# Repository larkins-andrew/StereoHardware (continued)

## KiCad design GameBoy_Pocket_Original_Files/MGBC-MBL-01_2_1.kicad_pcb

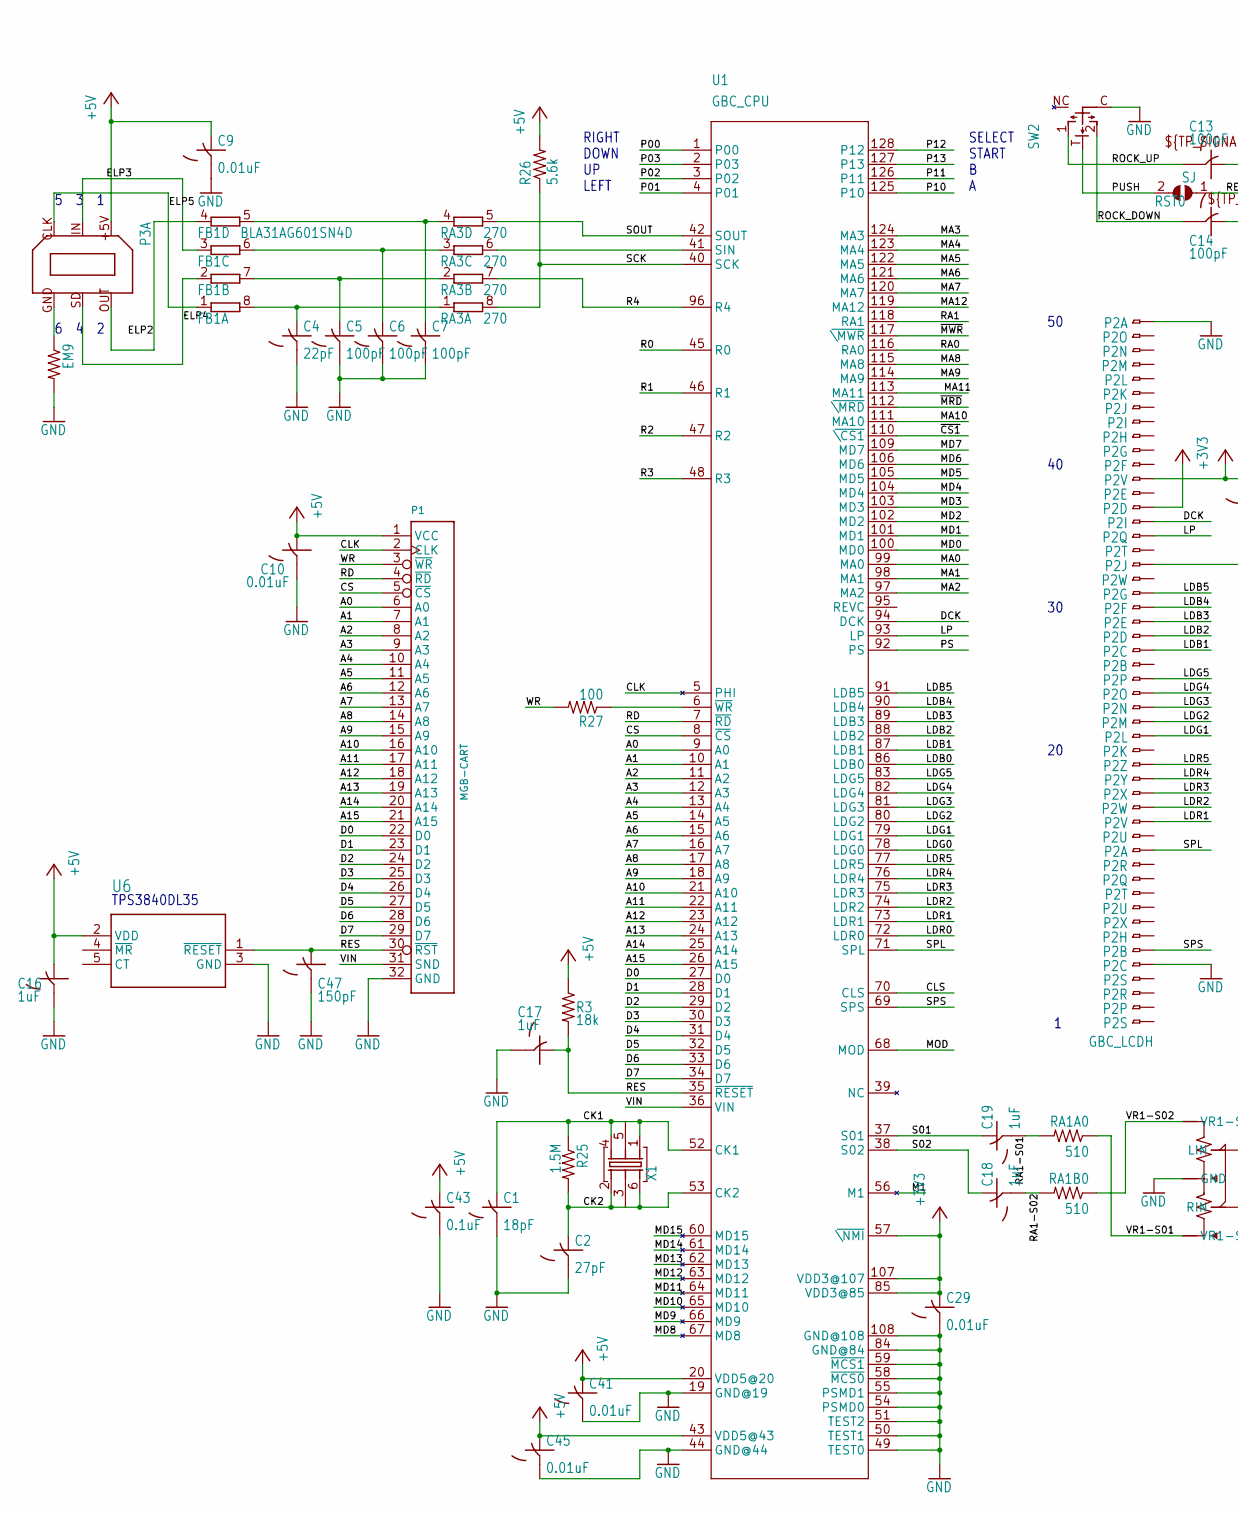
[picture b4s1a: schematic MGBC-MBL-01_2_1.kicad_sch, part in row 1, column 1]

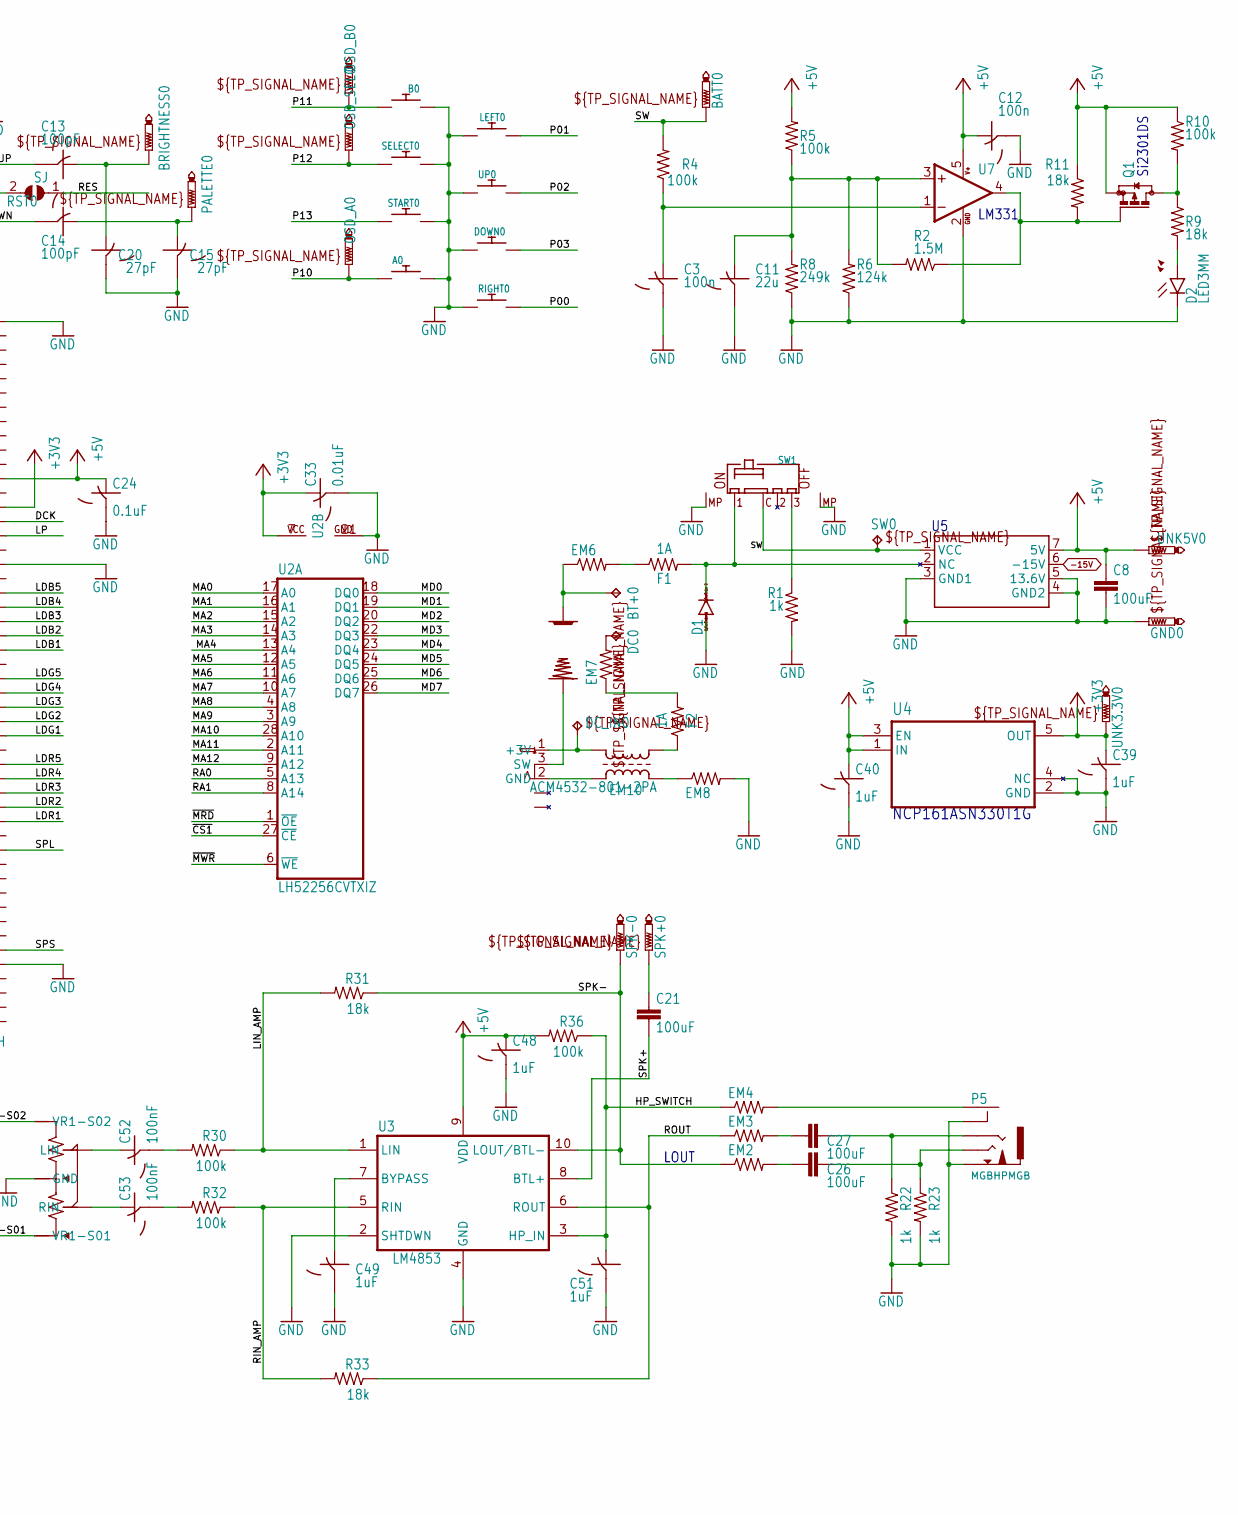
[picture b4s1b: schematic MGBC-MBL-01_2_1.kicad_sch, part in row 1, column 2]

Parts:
+0: MGB+BATTERY4
-0: MGB-BATTERY4
A0: DMG-BTN; DMG_BTN3
B0: DMG-BTN; DMG_BTN3
BATT0: PTR1TP20R; TP20R
BRIGHTNESS0: PTR1TP20R; TP20R
BT+0: TPPAD1-13; P1-13
C1: 18pF; C0603
C2, C15, C20: 27pF; C0603
C3, C12: 100n; C0603
C4: 22pF; C0603
C5, C6, C7, C13, C14: 100pF; C0603
C8, C21, C26, C27: 100uF; C1210
C9, C10, C29, C33, C41, C45: 0.01uF; C0603
C11: 22u; C0805
C16, C17, C18, C19, C39, C40, C48, C49, C51: 1uF; C0603
C24, C43: 0.1uF; C0603
C47: 150pF; C0603
C52, C53: 100nF; C0603
D1: CGRM400-G; SOD-123_MINI-SMA
D2: LED3MM
DC0: TPPAD1-13; P1-13
DC_IN0: TPTP20R; TP20R
DOWN0: DMG-BTN; MGB_BTN1_2
EM2, EM3, EM4, EM9: BLM18BD102SN1D; R0603
EM6, EM7, EM8: Z0805C221BPWZT; R0805
EM10: ACM4532-801-2PA; ACM4532
F1, F2: 1A; R0603
FB1: BLA31AG601SN4D; EXB38V
GND0: PTR1B1,27; B1,27
LEFT0: DMG-BTN; MGB_BTN1_2
OSD_A0: PTR1TP20R; TP20R
OSD_B0: PTR1TP20R; TP20R
OSD_SEL0: PTR1TP20R; TP20R
P1: MGB-CART
P2: GBC_LCDH; 62684-502100AHLF
P3: LINKPORTDMG-LINK-SHORT; CGB-LINK
P4: MGB-PWRJACK
P5: MGBHPMGB; MGB-HEADPHONE
PALETTE0: PTR1TP20R; TP20R
Q1: BSS84; SOT23
R1, R22, R23: 1k; R0603
R2, R25: 1.5M; R0603
R3, R9, R11, R31, R33: 18k; R0603
R4, R5, R10, R30, R32, R36: 100k; R0603
R6: 124k; R0603
R8: 249k; R0603
R26: 5.6k; R0603
R27: 100; R0603
RA1A0, RA1B0: 510; R0603
RA3: 270; EXB38V
RIGHT0: DMG-BTN; MGB_BTN1_2
RST0: SJ
SELECT0: DMG-BTN; DMG_BTN1_W2
SPK+0: PTR1PAD1-13; P1-13
SPK-0: PTR1PAD1-13; P1-13
START0: DMG-BTN; DMG_BTN1_W2
SW0: TPTP20R; TP20R
SW1: MGB-SW1; MGB-SWITCH
SW2: NAV_SWITCH
U1: GBC_CPU; QFP-128
U2: LH52256CVTXIZ; TSOP1-28
U3: LM4853; VSSOP10
U4: TLV70233QDBVRQ1; SOT95P280X145-5N
U5: MGB-PWR_BD; MGB-PWRBD
U6: TPS3840; SOT-23-5
U7: TL331; DBV-R-PDSO-G5
UNK3.3V0, UNK5V0: PTR1B1,27; B1,27
UP0: DMG-BTN; MGB_BTN1_2
VR1: MGB-POT""; MGB-POT
X1: 8.388608MHZ-4-PAD; 7.5X5-4-PAD

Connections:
+3V3: C29.1, C33.1, C39.1, P2.37, U1.57 (~\NMI), U1.85 (VDD3@85), U1.107 (VDD3@107), U2.7 (VCC), U4.5 (OUT), UNK3.3V0.TP
+5V: C8.1, C9.1, C10.1, C12.1, C16.1, C24.1, C40.1, C41.1, C43.1, C45.1, C48.1, P1.1 (VCC), P2.39, P3.+5V, Q1.2 (S), R3.1, R5.2, R10.1, R11.1, R26.2, R36.2, U1.20 (VDD5@20), U1.43 (VDD5@43), U3.9 (VDD), U4.1 (IN), U4.3 (EN), U5.7 (5V), U6.2 (VDD), U7.5 (V+), UNK5V0.TP; also elsewhere on the board
-15V: U5.6 (-15V)
A0: P1.6 (A0), U1.9 (A0)
A1: P1.7 (A1), U1.10 (A1)
A2: P1.8 (A2), U1.11 (A2)
A3: P1.9 (A3), U1.12 (A3)
A4: P1.10 (A4), U1.13 (A4)
A5: P1.11 (A5), U1.14 (A5)
A6: P1.12 (A6), U1.15 (A6)
A7: P1.13 (A7), U1.16 (A7)
A8: P1.14 (A8), U1.17 (A8)
A9: P1.15 (A9), U1.18 (A9)
A10: P1.16 (A10), U1.21 (A10)
A11: P1.17 (A11), U1.22 (A11)
A12: P1.18 (A12), U1.23 (A12)
A13: P1.19 (A13), U1.24 (A13)
A14: P1.20 (A14), U1.25 (A14)
A15: P1.21 (A15), U1.26 (A15)
BATT: +0.P$1, +0.P$2, +0.P$3, BT+0.TP, EM6.1
BATT_LVL: Q1.1 (G), R2.1, R11.2, U7.4 (OUT)
BATT_SENSE: C3.1, R4.1, U7.1 (-IN)
BATT_TH: C11.1, R2.2, R5.1, R6.2, R8.2, U7.3 (+IN)
CK1: C1.1, R25.1, U1.52 (CK1), X1.1, X1.4, X1.5
CK2: C2.1, R25.2, U1.53 (CK2), X1.2, X1.3, X1.6
CLK: P1.2 (CLK), U1.5 (PHI)
CLS: U1.70 (CLS)
CS: P1.5 (~CS), U1.8 (~CS)
D0: P1.22 (D0), U1.27 (D0)
D1: P1.23 (D1), U1.28 (D1)
D2: P1.24 (D2), U1.29 (D2)
D3: P1.25 (D3), U1.30 (D3)
D4: P1.26 (D4), U1.31 (D4)
D5: P1.27 (D5), U1.32 (D5)
D6: P1.28 (D6), U1.33 (D6)
D7: P1.29 (D7), U1.34 (D7)
DCK: P2.36, U1.94 (DCK)
ELP2: FB1.4 (1), P3.OUT
ELP3: FB1.3 (1), P3.IN
ELP4: FB1.2 (1), P3.SD
ELP5: FB1.1, P3.CLK
EM10_GND: EM10.3, P4.2 (GND)
EM10_POS: DC_IN0.TP, EM10.4, P4.1 (+3V)
GND: A0.P$2, B0.P$1, C1.2, C2.2, C3.2, C4.2, C5.2, C6.2, C7.2, C8.2, C9.2, C10.2, C11.2, C12.2, C15.2, C16.2, C17.2, C20.2, C24.2, C29.2, C33.2, C39.2, C40.2, C41.2, C43.2, C45.2, C47.2, C48.2, C49.2, C51.2, D1.A, D2.K (C), DOWN0.P$2, EM8.2, EM9.2, GND0.TP, LEFT0.P$2, P1.32 (GND), P2.5, P2.33, P2.50, P3.P$7 (GND), P3.P$10 (GND), P5.GND (S), P5.SWGND (SWB), R1.2, R6.1, R8.1, R22.2, R23.2, RIGHT0.P$1, SELECT0.P$1, START0.P$1, SW1.P$MP1 (MP1), SW1.P$MP2 (MP2), SW2.C, U1.19 (GND@19), U1.44 (GND@44), U1.49 (TEST0), U1.50 (TEST1), U1.51 (TEST2), U1.54 (PSMD0), U1.55 (PSMD1), U1.58 (~MCS0), U1.59 (~MCS1), U1.84 (GND@84), U1.108 (GND@108), U2.21 (GND), U3.2 (SHTDWN), U3.4 (GND), U4.2 (GND), U4.4 (NC), U5.3 (GND1), U5.4 (GND2), U5.5 (13.6V), U6.3 (GND), U7.2 (GND), UP0.P$1, VR1.P$1 (GND), VR1.P$6 (GND), VR1.P$7 (GND); also elsewhere on the board
HP_SWITCH: C51.1, EM4.1, R36.1, U3.3 (HP_IN)
LDB0: U1.86 (LDB0)
LDB1: P2.27, U1.87 (LDB1)
LDB2: P2.28, U1.88 (LDB2)
LDB3: P2.29, U1.89 (LDB3)
LDB4: P2.30, U1.90 (LDB4)
LDB5: P2.31, U1.91 (LDB5)
LDG0: U1.78 (LDG0)
LDG1: P2.21, U1.79 (LDG1)
LDG2: P2.22, U1.80 (LDG2)
LDG3: P2.23, U1.81 (LDG3)
LDG4: P2.24, U1.82 (LDG4)
LDG5: P2.25, U1.83 (LDG5)
LDR0: U1.72 (LDR0)
LDR1: P2.15, U1.73 (LDR1)
LDR2: P2.16, U1.74 (LDR2)
LDR3: P2.17, U1.75 (LDR3)
LDR4: P2.18, U1.76 (LDR4)
LDR5: P2.19, U1.77 (LDR5)
LIN_AMP: R30.1, R31.2, U3.1 (LIN)
LP: P2.35, U1.93 (LP)
M1: U1.56 (M1)
MA0: U1.99 (MA0), U2.17 (A0)
MA1: U1.98 (MA1), U2.16 (A1)
MA2: U1.97 (MA2), U2.15 (A2)
MA3: U1.124 (MA3), U2.14 (A3)
MA4: U1.123 (MA4), U2.13 (A4)
MA5: U1.122 (MA5), U2.12 (A5)
MA6: U1.121 (MA6), U2.11 (A6)
MA7: U1.120 (MA7), U2.10 (A7)
MA8: U1.115 (MA8), U2.4 (A8)
MA9: U1.114 (MA9), U2.3 (A9)
MA10: U1.111 (MA10), U2.28 (A10)
MA11: U1.113 (MA11), U2.2 (A11)
MA12: U1.119 (MA12), U2.9 (A12)
MD0: U1.100 (MD0), U2.18 (DQ0)
MD1: U1.101 (MD1), U2.19 (DQ1)
MD2: U1.102 (MD2), U2.20 (DQ2)
MD3: U1.103 (MD3), U2.22 (DQ3)
MD4: U1.104 (MD4), U2.23 (DQ4)
MD5: U1.105 (MD5), U2.24 (DQ5)
MD6: U1.106 (MD6), U2.25 (DQ6)
MD7: U1.109 (MD7), U2.26 (DQ7)
MD8: U1.67 (MD8)
MD9: U1.66 (MD9)
MD10: U1.65 (MD10)
MD11: U1.64 (MD11)
MD12: U1.63 (MD12)
MD13: U1.62 (MD13)
MD14: U1.61 (MD14)
MD15: U1.60 (MD15)
MOD: U1.68 (MOD)
unnamed: C7.1, FB1.5 (2), RA3.4 (1)
unnamed: C6.1, FB1.6 (2), RA3.3 (1)
unnamed: D2.A, R9.2
unnamed: C52.2, R30.2
unnamed: C53.2, R32.2
unnamed: C5.1, FB1.7 (2), RA3.2 (1)
unnamed: C52.1, VR1.P$3 (LIN)
unnamed: R27.1, U1.6 (~WR)
unnamed: C4.1, FB1.8 (2), RA3.1
unnamed: C53.1, VR1.P$2 (RIN)
unnamed: R1.1, SW1.P$3 (3)
unnamed: DC0.TP, EM7.2
unnamed: EM7.1, F2.2
unnamed: D1.C, F1.2, SW1.P$1 (1), U5.2 (NC)
unnamed: EM6.2, F1.1
unnamed: EM10.1, F2.1
unnamed: RA3.6 (2), U1.41 (SIN)
unnamed: Q1.3 (D), R9.1, R10.2
unnamed: EM8.1, EM10.2
unnamed: BRIGHTNESS0.TP, C13.1, C20.1
unnamed: EM9.1, P3.GND
unnamed: C14.1, C15.1, PALETTE0.TP
unnamed: C49.1, U3.7 (BYPASS)
unnamed: EM4.2, P5.SW (SWA)
unnamed: C27.2, P5.R, R22.1
unnamed: C26.2, P5.L (T), R23.1
unnamed: C26.1, EM2.2
unnamed: C27.1, EM3.2
unnamed: C21.1, SPK+0.TP
P00: RIGHT0.P$2, U1.1 (P00)
P01: LEFT0.P$1, U1.4 (P01)
P02: U1.3 (P02), UP0.P$2
P03: DOWN0.P$1, U1.2 (P03)
P10: A0.P$1, OSD_A0.TP, U1.125 (P10)
P11: B0.P$2, OSD_B0.TP, U1.126 (P11)
P12: OSD_SEL0.TP, SELECT0.P$2, U1.128 (P12)
P13: START0.P$2, U1.127 (P13)
PS: U1.92 (PS)
PUSH: RST0.2, SW2.T
R0: U1.45 (R0)
R1: U1.46 (R1)
R2: U1.47 (R2)
R3: U1.48 (R3)
R4: RA3.7 (2), U1.96 (R4)
RA0: U1.116 (RA0), U2.5 (A13)
RA1: U1.118 (RA1), U2.8 (A14)
RA1-S01: C19.2, RA1A0.2
RA1-S02: C18.2, RA1B0.2
RD: P1.4 (~RD), U1.7 (~RD)
RES: C17.1, C47.1, P1.30 (~RST), R3.2, RST0.1, U1.35 (~RESET), U6.1 (~RESET)
RIN_AMP: R32.1, R33.2, U3.5 (RIN)
ROCK_DOWN: C14.2, SW2.2
ROCK_UP: C13.2, SW2.1
ROUT: EM3.1, R33.1, U3.6 (ROUT)
S01: C19.1, U1.37 (S01)
S02: C18.1, U1.38 (S02)
SCK: R26.1, RA3.8 (2), U1.40 (SCK)
SOUT: RA3.5 (2), U1.42 (SOUT)
SPK+: C21.2, U3.8 (BTL+)
SPK-: EM2.1, R31.1, SPK-0.TP, U3.10 (LOUT/BTL-)
SPL: P2.13, U1.71 (SPL)
SPS: P2.6, U1.69 (SPS)
SW: BATT0.TP, R4.2, SW0.TP, SW1.P$C (C), U5.1 (VCC)
SW1B: -0.P$1, -0.P$3, -0.P$4, P4.3 (SW)
VIN: P1.31 (SND), U1.36 (VIN)
VR1-S01: RA1A0.1, VR1.P$5 (VR1-S01)
VR1-S02: RA1B0.1, VR1.P$4 (VR1-S02)
WR: P1.3 (~WR), R27.2
~CS1: U1.110 (~\CS1), U2.27 (~CE)
~MRD: U1.112 (~\MRD), U2.1 (~OE)
~MWR: U1.117 (~\MWR), U2.6 (~WE)

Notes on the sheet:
LM331
Si2301DS
NCP161ASN330T1G
5 3 1
SELECT START B A
LOUT
6 4 2
RIGHT DOWN UP LEFT
TPS3840DL35

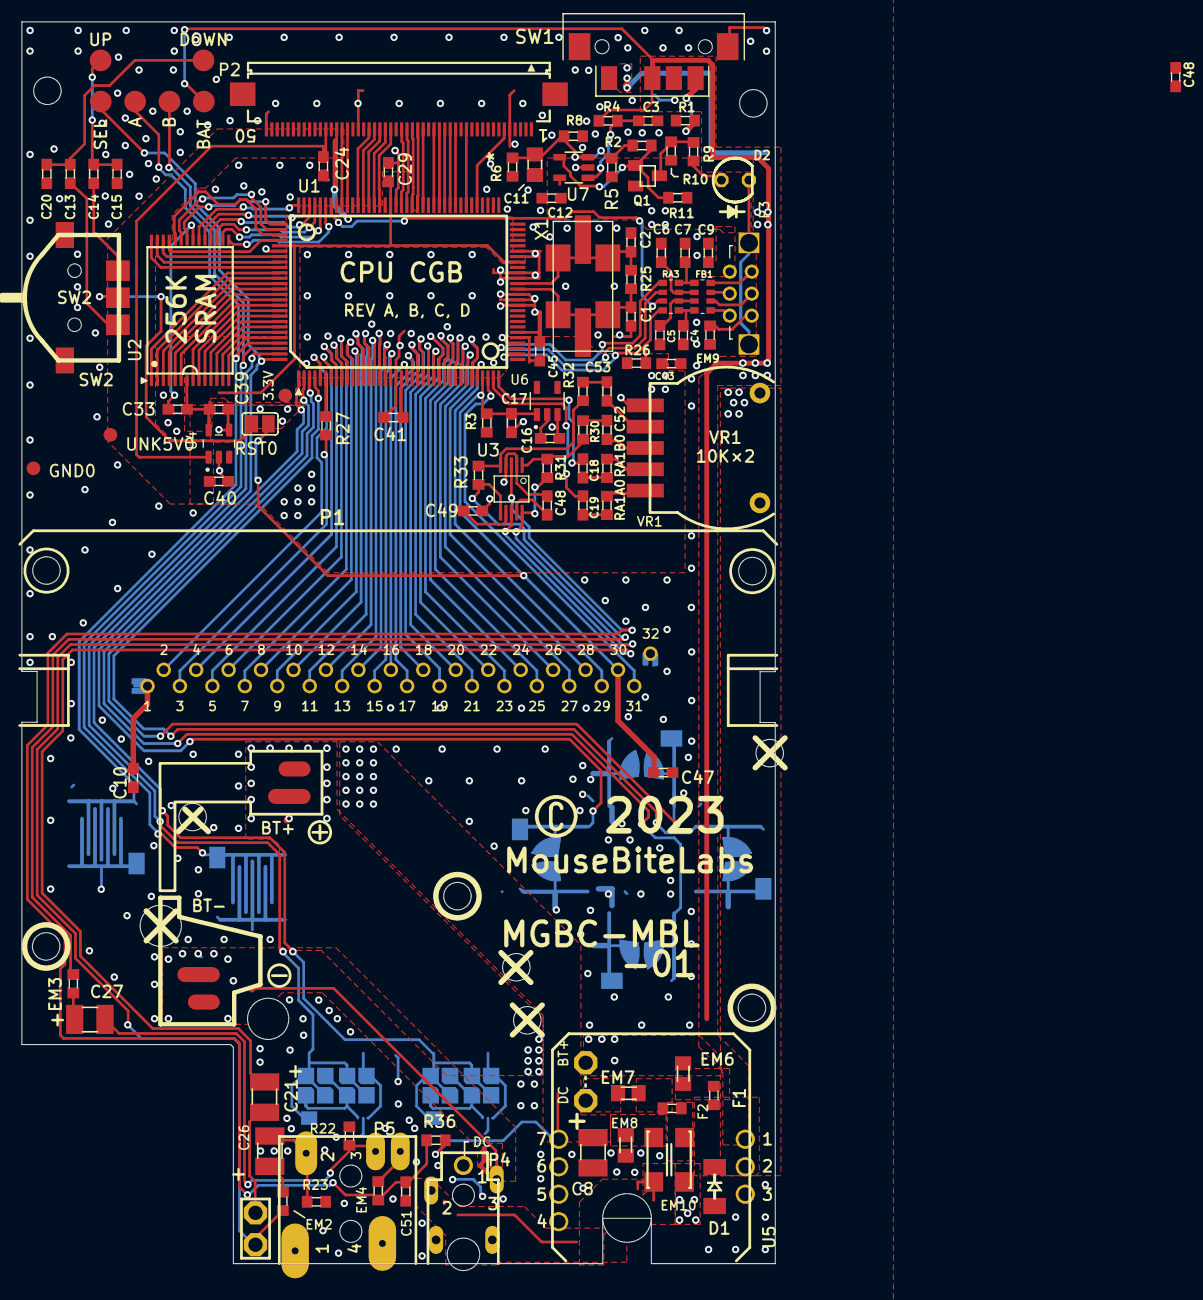
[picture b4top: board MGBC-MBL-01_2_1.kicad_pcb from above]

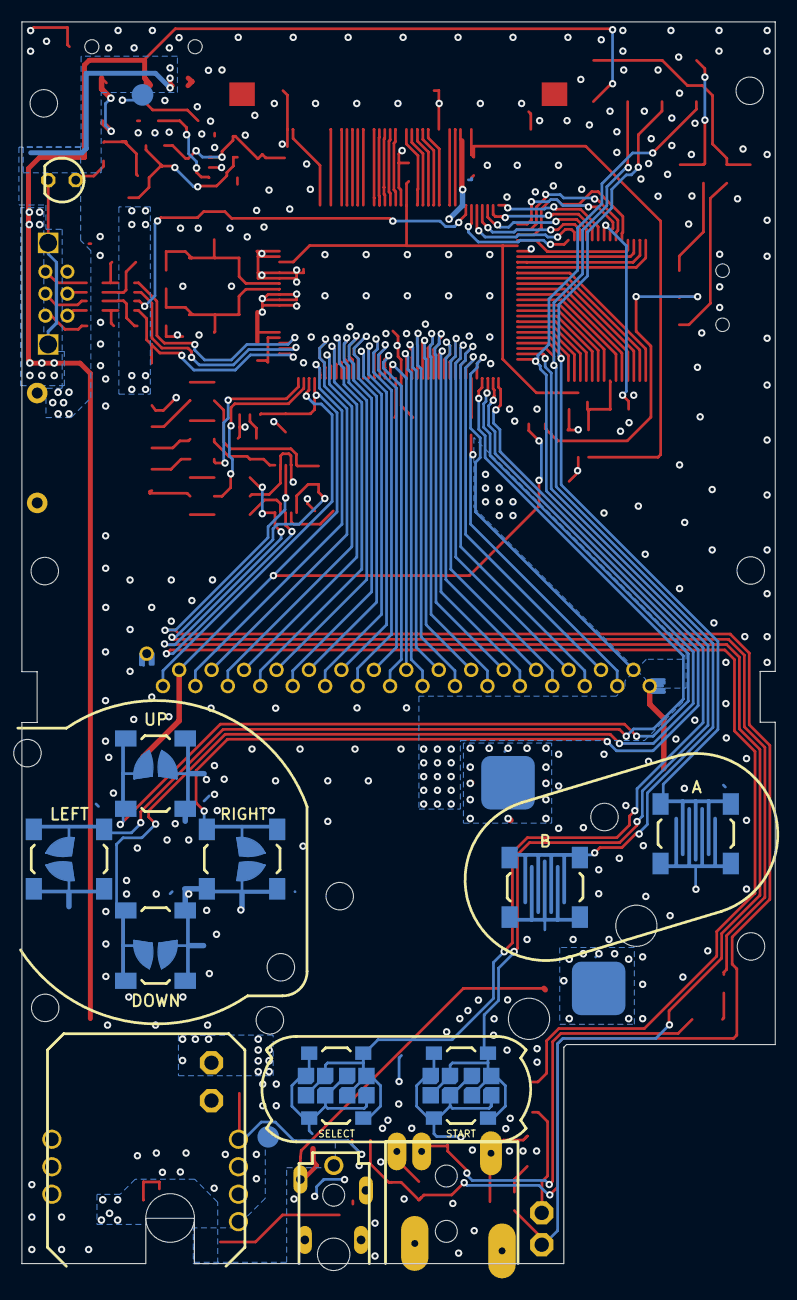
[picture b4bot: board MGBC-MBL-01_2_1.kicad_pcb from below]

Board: 2 copper layers, 69.6 x 114.8 mm, 131 parts (11 on the bottom side), 147 nets.

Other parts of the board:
C48#2: 1uF; C0603
UNK_HOLE_0: dummyfp0
UNK_HOLE_1: dummyfp1
UNK_HOLE_2: dummyfp2
UNK_HOLE_3: dummyfp3
UNK_HOLE_4: dummyfp4
UNK_HOLE_5: dummyfp5
UNK_HOLE_6: dummyfp6
UNK_HOLE_7: dummyfp7
UNK_HOLE_8: dummyfp8
UNK_HOLE_9: dummyfp9
UNK_HOLE_10: dummyfp10
UNK_HOLE_11: dummyfp11
UNK_HOLE_12: dummyfp12
UNK_HOLE_13: dummyfp13

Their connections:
+5V: C48#2.1; also elsewhere on the board
GND: C48#2.2; also elsewhere on the board

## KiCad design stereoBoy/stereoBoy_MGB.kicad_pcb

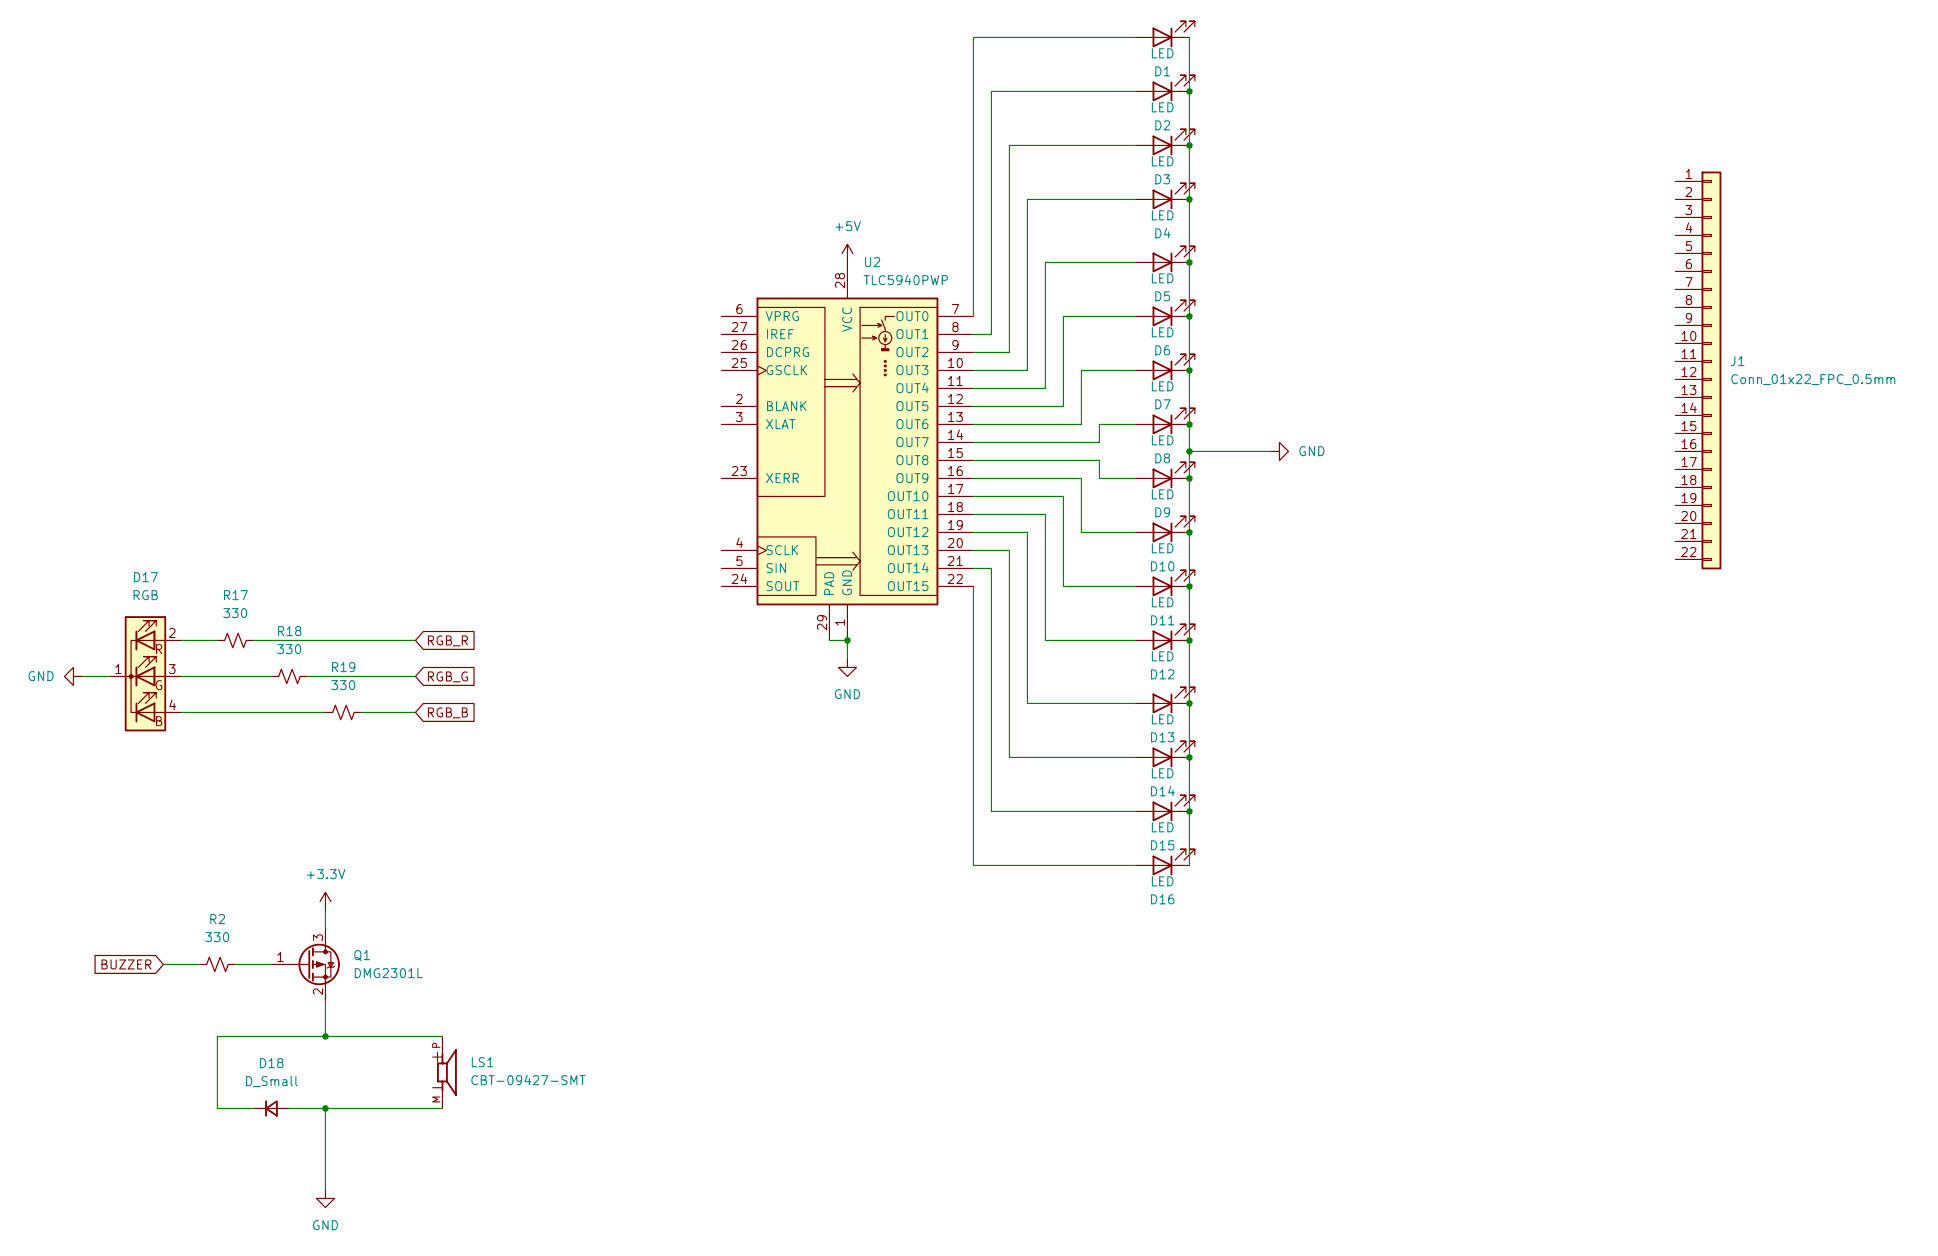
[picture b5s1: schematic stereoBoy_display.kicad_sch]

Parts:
D1, D2, D3, D4, D5, D6, D7, D8, D9, D10, D11, D12, D13, D14, D15, D16: LED; LED_D3.0mm
D17: RGB; LED_WS2812B-Mini_PLCC4_3.5x3.5mm
D18: D_Small; D_0603_1608Metric
J1: Conn_01x22_FPC_0.5mm; FPC_1x22_P0.5mm_Horizontal_BottomContact
LS1: CBT-09427-SMT; CBT_09427_SMT_TR
Q1: DMG2301L; SOT-23
R2, R17, R18, R19: 330; R_0603_1608Metric
U2: TLC5940PWP; HTSSOP-28-1EP_4.4x9.7mm_P0.65mm_EP2.85x5.4mm

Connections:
+3.3V: Q1.3 (D)
+5V: U2.28 (VCC); also elsewhere on the board
BUZZER: R2.1
GND: D1.1 (K), D2.1 (K), D3.1 (K), D4.1 (K), D5.1 (K), D6.1 (K), D7.1 (K), D8.1 (K), D9.1 (K), D10.1 (K), D11.1 (K), D12.1 (K), D13.1 (K), D14.1 (K), D15.1 (K), D16.1 (K), D17.1 (K), D18.2 (A), LS1.M, U2.1 (GND), U2.29 (PAD); also elsewhere on the board
unnamed: D1.2 (A), U2.7 (OUT0)
unnamed: D2.2 (A), U2.8 (OUT1)
unnamed: D3.2 (A), U2.9 (OUT2)
unnamed: D4.2 (A), U2.10 (OUT3)
unnamed: D5.2 (A), U2.11 (OUT4)
unnamed: D6.2 (A), U2.12 (OUT5)
unnamed: D7.2 (A), U2.13 (OUT6)
unnamed: D8.2 (A), U2.14 (OUT7)
unnamed: D9.2 (A), U2.15 (OUT8)
unnamed: D10.2 (A), U2.16 (OUT9)
unnamed: D11.2 (A), U2.17 (OUT10)
unnamed: D12.2 (A), U2.18 (OUT11)
unnamed: D13.2 (A), U2.19 (OUT12)
unnamed: D14.2 (A), U2.20 (OUT13)
unnamed: D15.2 (A), U2.21 (OUT14)
unnamed: D16.2 (A), U2.22 (OUT15)
unnamed: D17.4 (BA), R19.1
unnamed: D17.3 (GA), R18.1
unnamed: D17.2 (RA), R17.1
unnamed: D18.1 (K), LS1.P, Q1.2 (S)
unnamed: Q1.1 (G), R2.2
RGB_B: R19.2
RGB_G: R18.2
RGB_R: R17.2

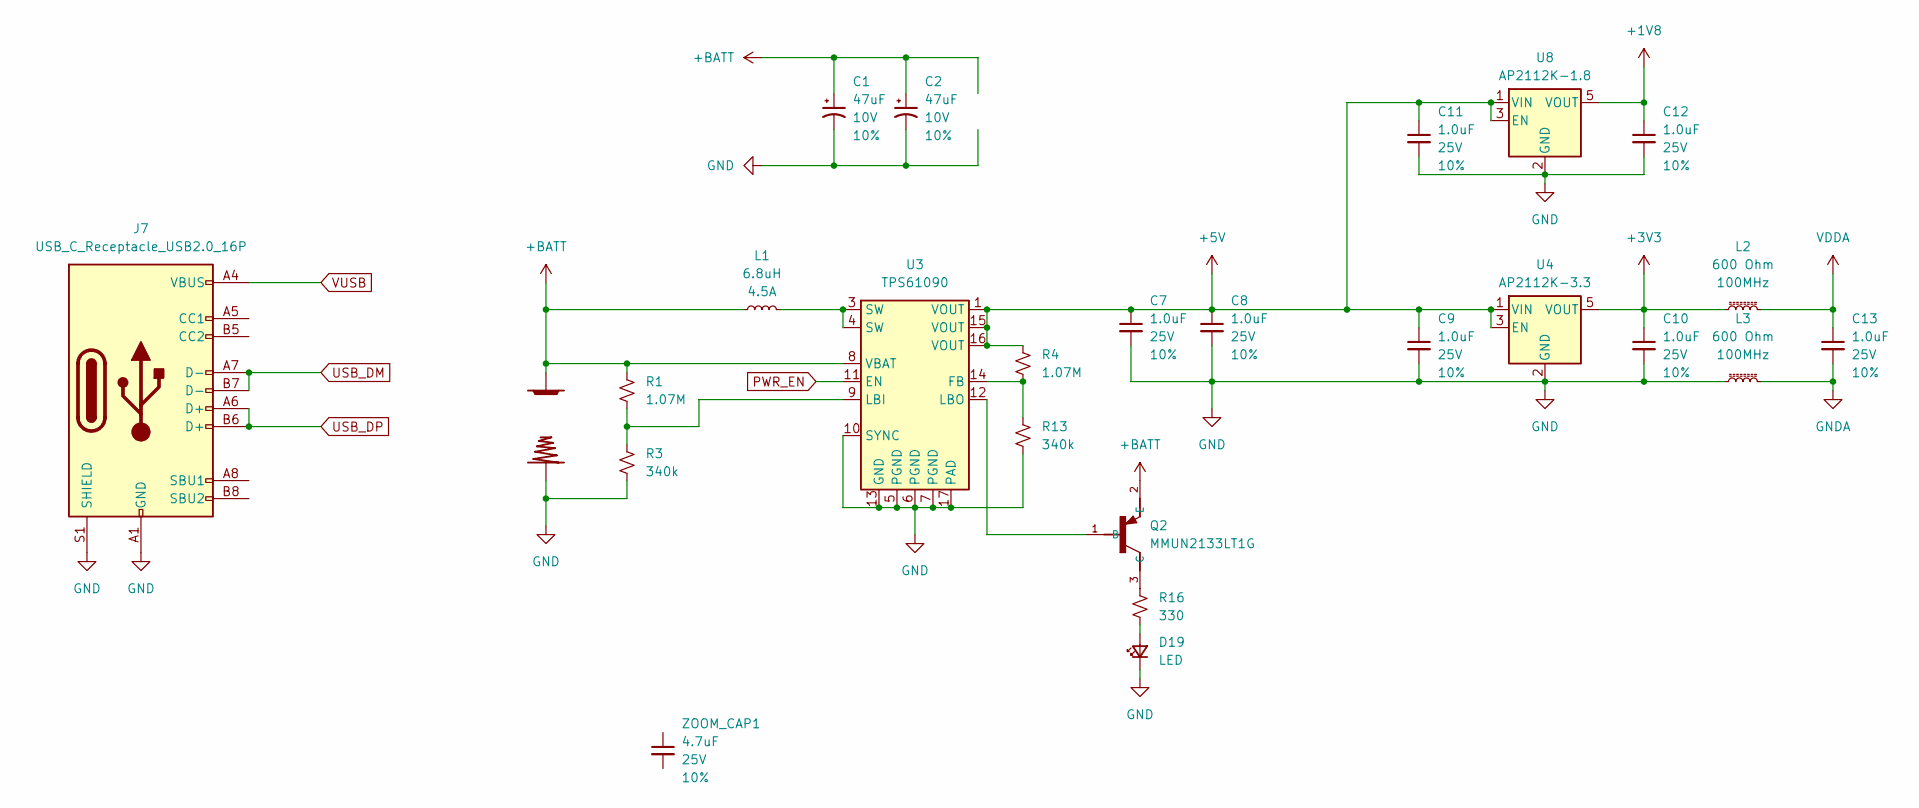
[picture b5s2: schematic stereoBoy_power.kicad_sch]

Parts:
+0: MGB+BATTERY4
-0: MGB-BATTERY4
C1, C2: 47uF; CP_EIA-7343-15_Kemet-W_HandSolder; Voltage 10V; Tolerance 10%
C7, C8, C9, C10, C11, C12, C13: 1.0uF; C_0805_2012Metric; Voltage 25V; Tolerance 10%
D19: LED; LED_0603_1608Metric
J7: USB_C_Receptacle_USB2.0_16P; USB_C_Receptacle_GCT_USB4105-xx-A_16P_TopMnt_Horizontal
L1: 6.8uH; Inductor_7.3x6.6mm
L2, L3: 600 Ohm; C_0805_2012Metric
Q2: MMUN2133LT1G; SOT95P240X111-3N
R1, R4: 1.07M; R_0603_1608Metric
R3, R13: 340k; R_0603_1608Metric
R16: 330; R_0603_1608Metric
U3: TPS61090; Texas_RSA_VQFN-16-1EP_4x4mm_P0.65mm_EP2.7x2.7mm_ThermalVias
U4: AP2112K-3.3; SOT-23-5
U8: AP2112K-1.8; SOT-23-5
ZOOM_CAP1: 4.7uF; C_0805_2012Metric; Voltage 25V; Tolerance 10%

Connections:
+1V8: C12.1, U8.5 (VOUT); also elsewhere on the board
+3V3: C10.1, L2.1, U4.5 (VOUT); also elsewhere on the board
+5V: C7.1, C8.1, C9.1, C11.1, R4.1, U3.1 (VOUT), U3.15 (VOUT), U3.16 (VOUT), U4.1 (VIN), U4.3 (EN), U8.1 (VIN), U8.3 (EN); also elsewhere on the board
+BATT: +0.P$1, +0.P$2, +0.P$3, C1.1, C2.1, L1.1, Q2.2 (E), R1.1, U3.8 (VBAT)
GND: -0.P$1, -0.P$3, -0.P$4, C1.2, C2.2, C7.2, C8.2, C9.2, C10.2, C11.2, C12.2, D19.1 (K), J7.A1 (GND), J7.A12 (GND), J7.B1 (GND), J7.B12 (GND), J7.S1 (SHIELD), L3.1, R3.2, R13.2, U3.5 (PGND), U3.6 (PGND), U3.7 (PGND), U3.10 (SYNC), U3.13 (GND), U3.17 (PAD), U4.2 (GND), U8.2 (GND); also elsewhere on the board
GNDA: C13.2, L3.2; also elsewhere on the board
unnamed: D19.2 (A), R16.2
unnamed: L1.2, U3.3 (SW), U3.4 (SW)
unnamed: Q2.1 (B), U3.12 (LBO)
unnamed: Q2.3 (C), R16.1
unnamed: R4.2, R13.1, U3.14 (FB)
unnamed: R1.2, R3.1, U3.9 (LBI)
PWR_EN: U3.11 (EN)
USB_DM: J7.A7 (D-), J7.B7 (D-); also elsewhere on the board
USB_DP: J7.A6 (D+), J7.B6 (D+); also elsewhere on the board
VDDA: C13.1, L2.2; also elsewhere on the board
VUSB: J7.A4 (VBUS), J7.A9 (VBUS), J7.B4 (VBUS), J7.B9 (VBUS)

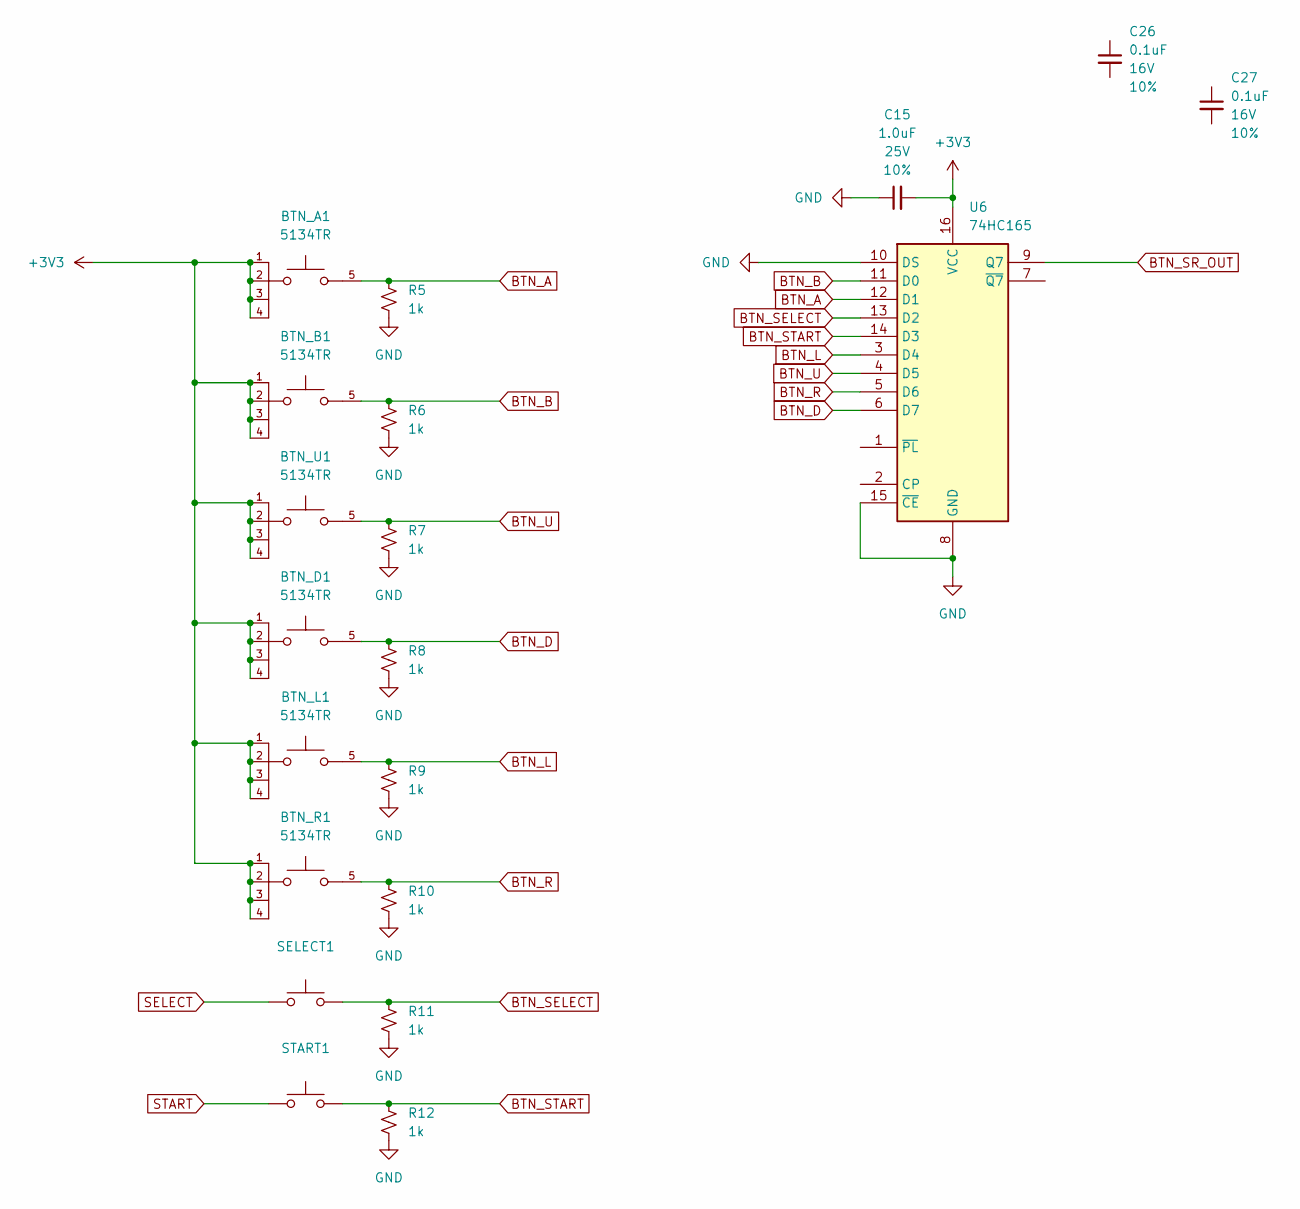
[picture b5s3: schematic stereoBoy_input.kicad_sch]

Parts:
BTN_A1: 5134TR; SNAP_DOME_SWITCH_7x7; PARTREV A
BTN_B1: 5134TR; SNAP_DOME_SWITCH_7x7; PARTREV A
BTN_D1: 5134TR; SNAP_DOME_SWITCH_7x7; PARTREV A
BTN_L1: 5134TR; SNAP_DOME_SWITCH_7x7; PARTREV A
BTN_R1: 5134TR; SNAP_DOME_SWITCH_7x7; PARTREV A
BTN_U1: 5134TR; SNAP_DOME_SWITCH_7x7; PARTREV A
C15: 1.0uF; C_0805_2012Metric; Voltage 25V; Tolerance 10%
C26, C27: 0.1uF; C_Elec_5x5.4; Voltage 16V; Tolerance 10%
R5, R6, R7, R8, R9, R10, R11, R12: 1k; R_0603_1608Metric
SELECT1: SMD_6x3.5mm_h2.5mm; MGB_BUTTONPAD_SELECTSTART; Mfg Part# 8-004 SMD Button 8x3.6mm Height=2.5mm
START1: SMD_6x3.5mm_h2.5mm; MGB_BUTTONPAD_SELECTSTART; Mfg Part# 8-004 SMD Button 8x3.6mm Height=2.5mm
U6: 74HC165; TSSOP-16_4.4x5mm_P0.65mm

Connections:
+3V3: BTN_A1.1, BTN_A1.2, BTN_A1.3, BTN_A1.4, BTN_B1.1, BTN_B1.2, BTN_B1.3, BTN_B1.4, BTN_D1.1, BTN_D1.2, BTN_D1.3, BTN_D1.4, BTN_L1.1, BTN_L1.2, BTN_L1.3, BTN_L1.4, BTN_R1.1, BTN_R1.2, BTN_R1.3, BTN_R1.4, BTN_U1.1, BTN_U1.2, BTN_U1.3, BTN_U1.4, C15.2, U6.16 (VCC); also elsewhere on the board
BTN_A: BTN_A1.5, R5.2, U6.12 (D1); also elsewhere on the board
BTN_B: BTN_B1.5, R6.2, U6.11 (D0); also elsewhere on the board
BTN_D: BTN_D1.5, R8.2, U6.6 (D7); also elsewhere on the board
BTN_L: BTN_L1.5, R9.2, U6.3 (D4); also elsewhere on the board
BTN_R: BTN_R1.5, R10.2, U6.5 (D6); also elsewhere on the board
BTN_SELECT: R11.2, SELECT1.2, U6.13 (D2); also elsewhere on the board
BTN_SR_OUT: U6.9 (Q7)
BTN_START: R12.2, START1.2, U6.14 (D3); also elsewhere on the board
BTN_U: BTN_U1.5, R7.2, U6.4 (D5); also elsewhere on the board
GND: C15.1, R5.1, R6.1, R7.1, R8.1, R9.1, R10.1, R11.1, R12.1, U6.8 (GND), U6.10 (DS), U6.15 (~CE); also elsewhere on the board
SELECT: SELECT1.1
START: START1.1
